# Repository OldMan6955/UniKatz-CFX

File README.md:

# UniKatz-CFX
UWU x CAT x Love x Peace is all we need

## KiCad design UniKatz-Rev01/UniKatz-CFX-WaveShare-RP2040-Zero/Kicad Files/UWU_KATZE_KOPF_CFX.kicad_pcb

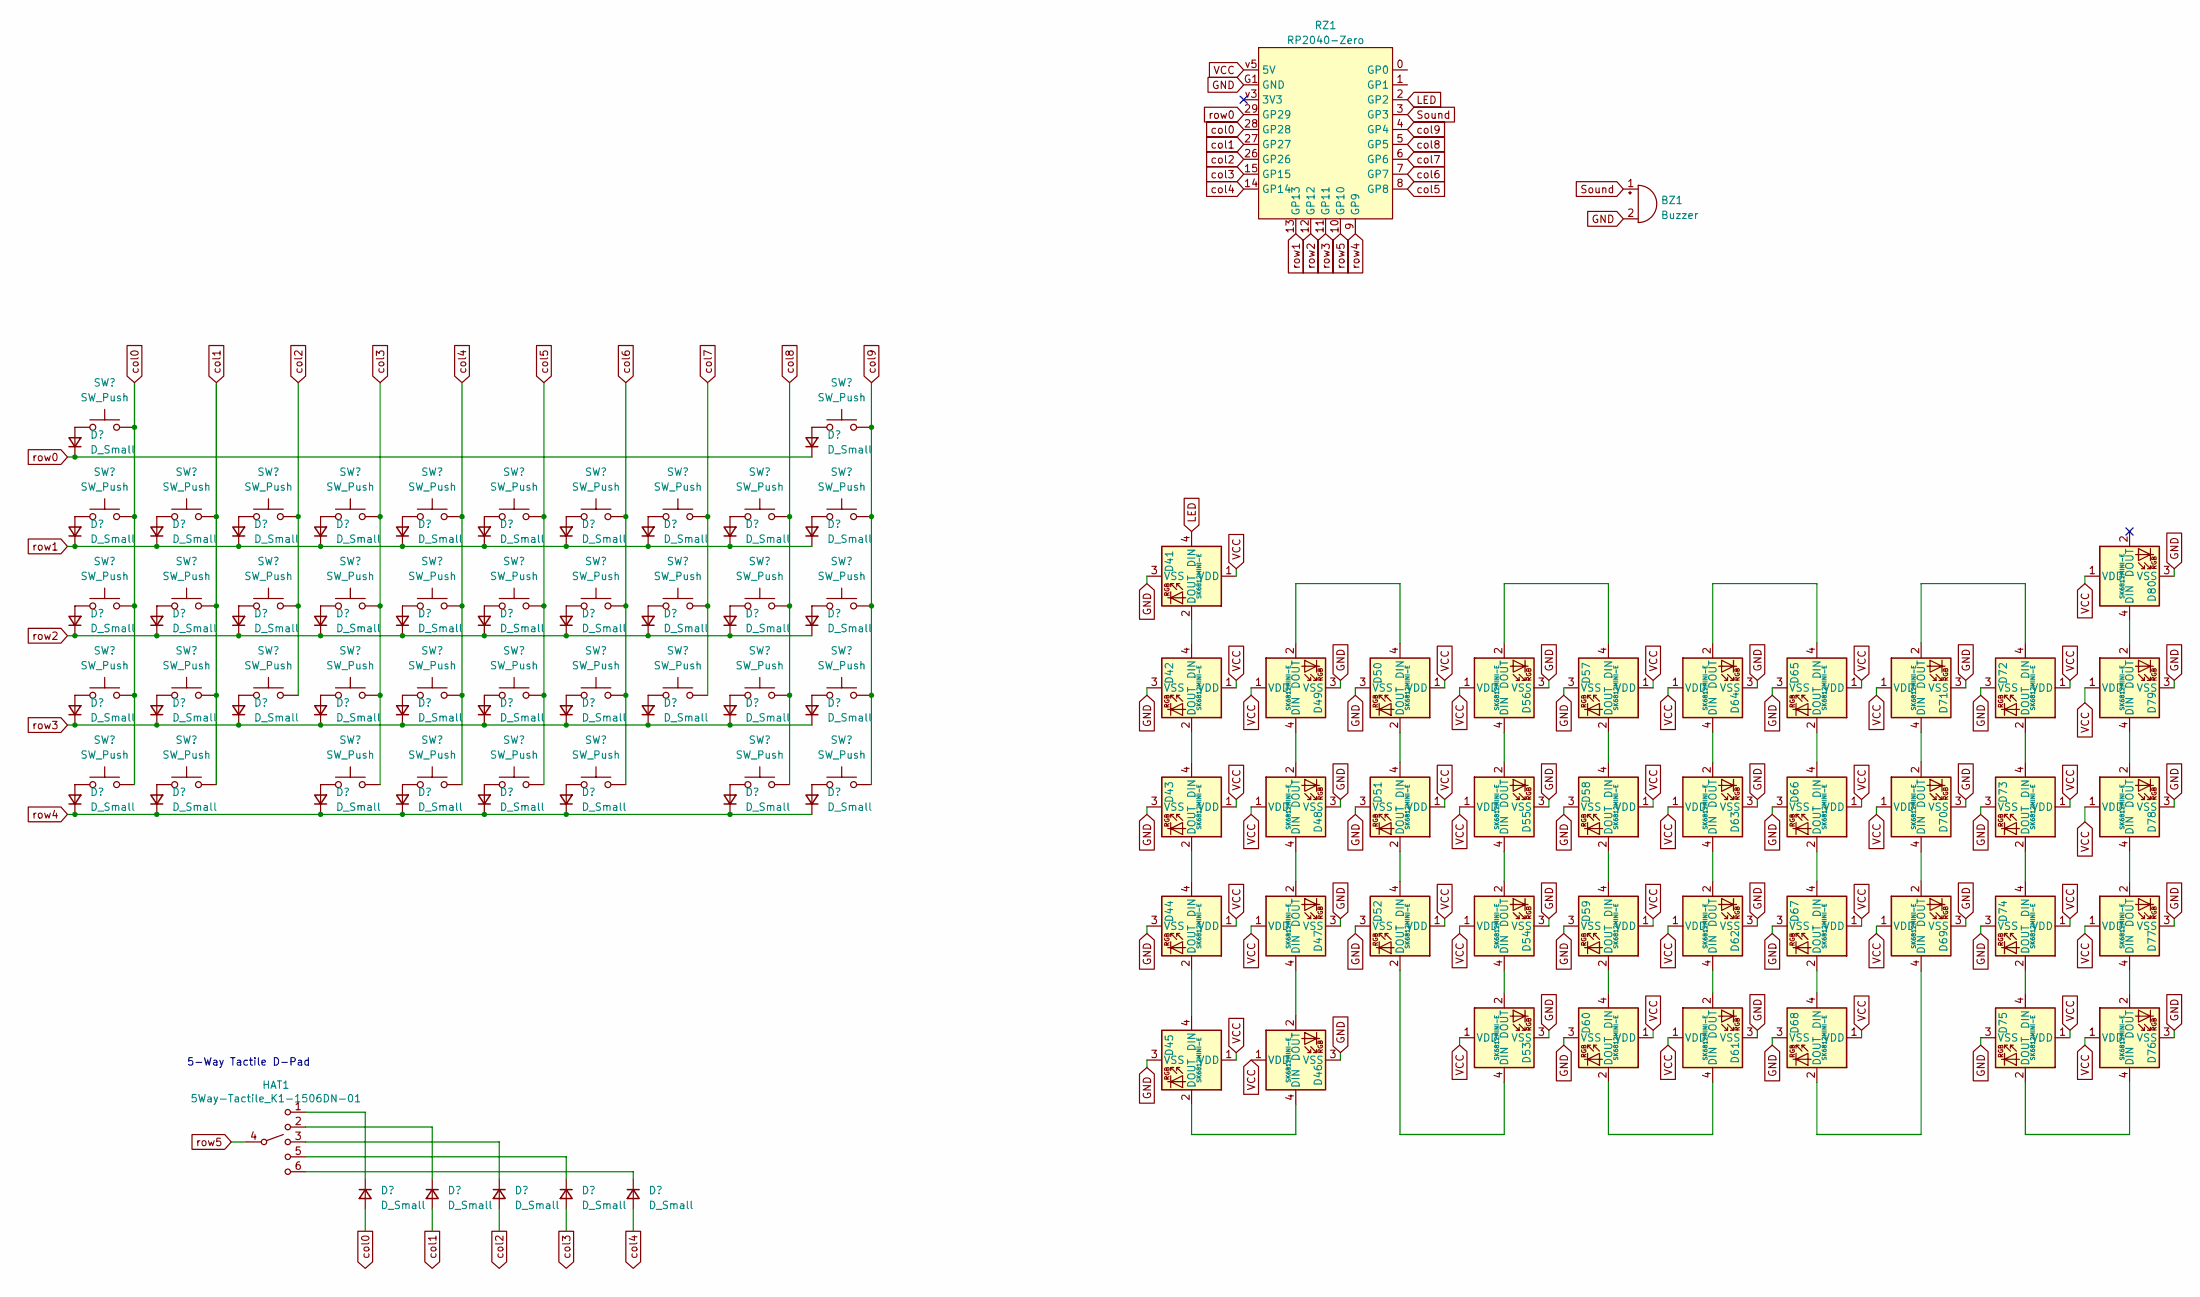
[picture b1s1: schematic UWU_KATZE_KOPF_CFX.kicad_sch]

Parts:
BZ1: Buzzer; Buzzer_Mallory_AST1109MLTRQ
D1, D2, D3, D4, D5, D6, D7, D8, D9, D10, D11, D12, D13, D14, D15, D16, D17, D18, D19, D20, D21, D22, D23, D24, D25, D26, D27, D28, D29, D30, D31, D32, D33, D34, D35, D36, D37, D38, D39, D40, D81, D82, D83, D84, D85: D_Small; Diode_SOD123 triangle clean
D41, D42, D43, D44, D45, D46, D47, D48, D49, D50, D51, D52, D53, D54, D55, D56, D57, D58, D59, D60, D61, D62, D63, D64, D65, D66, D67, D68, D69, D70, D71, D72, D73, D74, D75, D76, D77, D78, D79, D80: SK6812MINI-E; SK6812-MINI-E mit LED v2
HAT1: 5Way-Tactile_K1-1506DN-01; 5Way-non-reverse no silk
RZ1: RP2040-Zero; RP2040-Zero mittig
SW1, SW2, SW3, SW4, SW5, SW6, SW7, SW8, SW9, SW10, SW11, SW12, SW13, SW14, SW15, SW16, SW17, SW18, SW19, SW20, SW21, SW22, SW23, SW24, SW25, SW26, SW27, SW28, SW29, SW30, SW31, SW32, SW33, SW34, SW35, SW36, SW37, SW38, SW39, SW40: SW_Push; Kailh_socket_PG1350 LED Window ME Version V2

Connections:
GND: BZ1.2 (+), D41.3 (VSS), D42.3 (VSS), D43.3 (VSS), D44.3 (VSS), D45.3 (VSS), D46.3 (VSS), D47.3 (VSS), D48.3 (VSS), D49.3 (VSS), D50.3 (VSS), D51.3 (VSS), D52.3 (VSS), D53.3 (VSS), D54.3 (VSS), D55.3 (VSS), D56.3 (VSS), D57.3 (VSS), D58.3 (VSS), D59.3 (VSS), D60.3 (VSS), D61.3 (VSS), D62.3 (VSS), D63.3 (VSS), D64.3 (VSS), D65.3 (VSS), D66.3 (VSS), D67.3 (VSS), D68.3 (VSS), D69.3 (VSS), D70.3 (VSS), D71.3 (VSS), D72.3 (VSS), D73.3 (VSS), D74.3 (VSS), D75.3 (VSS), D76.3 (VSS), D77.3 (VSS), D78.3 (VSS), D79.3 (VSS), D80.3 (VSS), RZ1.G1 (GND)
LED: D41.4 (DIN), RZ1.2 (GP2)
unnamed: D1.2 (A), SW1.1
unnamed: D2.2 (A), SW2.1
unnamed: D3.2 (A), SW3.1
unnamed: D4.2 (A), SW4.1
unnamed: D5.2 (A), SW5.1
unnamed: D6.2 (A), SW6.1
unnamed: D7.2 (A), SW7.1
unnamed: D8.2 (A), SW8.1
unnamed: D9.2 (A), SW9.1
unnamed: D10.2 (A), SW10.1
unnamed: D11.2 (A), SW11.1
unnamed: D12.2 (A), SW12.1
unnamed: D13.2 (A), SW13.1
unnamed: D14.2 (A), SW14.1
unnamed: D15.2 (A), SW15.1
unnamed: D16.2 (A), SW16.1
unnamed: D17.2 (A), SW17.1
unnamed: D18.2 (A), SW18.1
unnamed: D19.2 (A), SW19.1
unnamed: D20.2 (A), SW20.1
unnamed: D21.2 (A), SW21.1
unnamed: D22.2 (A), SW22.1
unnamed: D23.2 (A), SW23.1
unnamed: D24.2 (A), SW24.1
unnamed: D25.2 (A), SW25.1
unnamed: D26.2 (A), SW26.1
unnamed: D27.2 (A), SW27.1
unnamed: D28.2 (A), SW28.1
unnamed: D29.2 (A), SW29.1
unnamed: D30.2 (A), SW30.1
unnamed: D31.2 (A), SW31.1
unnamed: D32.2 (A), SW32.1
unnamed: D33.2 (A), SW33.1
unnamed: D34.2 (A), SW34.1
unnamed: D35.2 (A), SW35.1
unnamed: D36.2 (A), SW36.1
unnamed: D37.2 (A), SW37.1
unnamed: D38.2 (A), SW38.1
unnamed: D39.2 (A), SW39.1
unnamed: D40.2 (A), SW40.1
unnamed: D41.2 (DOUT), D42.4 (DIN)
unnamed: D42.2 (DOUT), D43.4 (DIN)
unnamed: D43.2 (DOUT), D44.4 (DIN)
unnamed: D44.2 (DOUT), D45.4 (DIN)
unnamed: D45.2 (DOUT), D46.4 (DIN)
unnamed: D46.2 (DOUT), D47.4 (DIN)
unnamed: D47.2 (DOUT), D48.4 (DIN)
unnamed: D48.2 (DOUT), D49.4 (DIN)
unnamed: D49.2 (DOUT), D50.4 (DIN)
unnamed: D50.2 (DOUT), D51.4 (DIN)
unnamed: D51.2 (DOUT), D52.4 (DIN)
unnamed: D52.2 (DOUT), D53.4 (DIN)
unnamed: D53.2 (DOUT), D54.4 (DIN)
unnamed: D54.2 (DOUT), D55.4 (DIN)
unnamed: D55.2 (DOUT), D56.4 (DIN)
unnamed: D56.2 (DOUT), D57.4 (DIN)
unnamed: D57.2 (DOUT), D58.4 (DIN)
unnamed: D58.2 (DOUT), D59.4 (DIN)
unnamed: D59.2 (DOUT), D60.4 (DIN)
unnamed: D60.2 (DOUT), D61.4 (DIN)
unnamed: D61.2 (DOUT), D62.4 (DIN)
unnamed: D62.2 (DOUT), D63.4 (DIN)
unnamed: D63.2 (DOUT), D64.4 (DIN)
unnamed: D64.2 (DOUT), D65.4 (DIN)
unnamed: D65.2 (DOUT), D66.4 (DIN)
unnamed: D66.2 (DOUT), D67.4 (DIN)
unnamed: D67.2 (DOUT), D68.4 (DIN)
unnamed: D68.2 (DOUT), D69.4 (DIN)
unnamed: D69.2 (DOUT), D70.4 (DIN)
unnamed: D70.2 (DOUT), D71.4 (DIN)
unnamed: D71.2 (DOUT), D72.4 (DIN)
unnamed: D72.2 (DOUT), D73.4 (DIN)
unnamed: D73.2 (DOUT), D74.4 (DIN)
unnamed: D74.2 (DOUT), D75.4 (DIN)
unnamed: D75.2 (DOUT), D76.4 (DIN)
unnamed: D76.2 (DOUT), D77.4 (DIN)
unnamed: D77.2 (DOUT), D78.4 (DIN)
unnamed: D78.2 (DOUT), D79.4 (DIN)
unnamed: D79.2 (DOUT), D80.4 (DIN)
unnamed: D81.1 (K), HAT1.1
unnamed: D82.1 (K), HAT1.2
unnamed: D83.1 (K), HAT1.3
unnamed: D84.1 (K), HAT1.5
unnamed: D85.1 (K), HAT1.6
Sound: BZ1.1 (-), RZ1.3 (GP3)
VCC: D41.1 (VDD), D42.1 (VDD), D43.1 (VDD), D44.1 (VDD), D45.1 (VDD), D46.1 (VDD), D47.1 (VDD), D48.1 (VDD), D49.1 (VDD), D50.1 (VDD), D51.1 (VDD), D52.1 (VDD), D53.1 (VDD), D54.1 (VDD), D55.1 (VDD), D56.1 (VDD), D57.1 (VDD), D58.1 (VDD), D59.1 (VDD), D60.1 (VDD), D61.1 (VDD), D62.1 (VDD), D63.1 (VDD), D64.1 (VDD), D65.1 (VDD), D66.1 (VDD), D67.1 (VDD), D68.1 (VDD), D69.1 (VDD), D70.1 (VDD), D71.1 (VDD), D72.1 (VDD), D73.1 (VDD), D74.1 (VDD), D75.1 (VDD), D76.1 (VDD), D77.1 (VDD), D78.1 (VDD), D79.1 (VDD), D80.1 (VDD), RZ1.v5 (5V)
col0: D81.2 (A), RZ1.28 (GP28), SW1.2, SW3.2, SW13.2, SW23.2, SW33.2
col1: D82.2 (A), RZ1.27 (GP27), SW4.2, SW14.2, SW24.2, SW34.2
col2: D83.2 (A), RZ1.26 (GP26), SW5.2, SW15.2, SW25.2
col3: D84.2 (A), RZ1.15 (GP15), SW6.2, SW16.2, SW26.2, SW35.2
col4: D85.2 (A), RZ1.14 (GP14), SW7.2, SW17.2, SW27.2, SW36.2
col5: RZ1.8 (GP8), SW8.2, SW18.2, SW28.2, SW37.2
col6: RZ1.7 (GP7), SW9.2, SW19.2, SW29.2, SW38.2
col7: RZ1.6 (GP6), SW10.2, SW20.2, SW30.2
col8: RZ1.5 (GP5), SW11.2, SW21.2, SW31.2, SW39.2
col9: RZ1.4 (GP4), SW2.2, SW12.2, SW22.2, SW32.2, SW40.2
row0: D1.1 (K), D2.1 (K), RZ1.29 (GP29)
row1: D3.1 (K), D4.1 (K), D5.1 (K), D6.1 (K), D7.1 (K), D8.1 (K), D9.1 (K), D10.1 (K), D11.1 (K), D12.1 (K), RZ1.13 (GP13)
row2: D13.1 (K), D14.1 (K), D15.1 (K), D16.1 (K), D17.1 (K), D18.1 (K), D19.1 (K), D20.1 (K), D21.1 (K), D22.1 (K), RZ1.12 (GP12)
row3: D23.1 (K), D24.1 (K), D25.1 (K), D26.1 (K), D27.1 (K), D28.1 (K), D29.1 (K), D30.1 (K), D31.1 (K), D32.1 (K), RZ1.11 (GP11)
row4: D33.1 (K), D34.1 (K), D35.1 (K), D36.1 (K), D37.1 (K), D38.1 (K), D39.1 (K), D40.1 (K), RZ1.9 (GP9)
row5: HAT1.4, RZ1.10 (GP10)

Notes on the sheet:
5-Way Tactile D-Pad

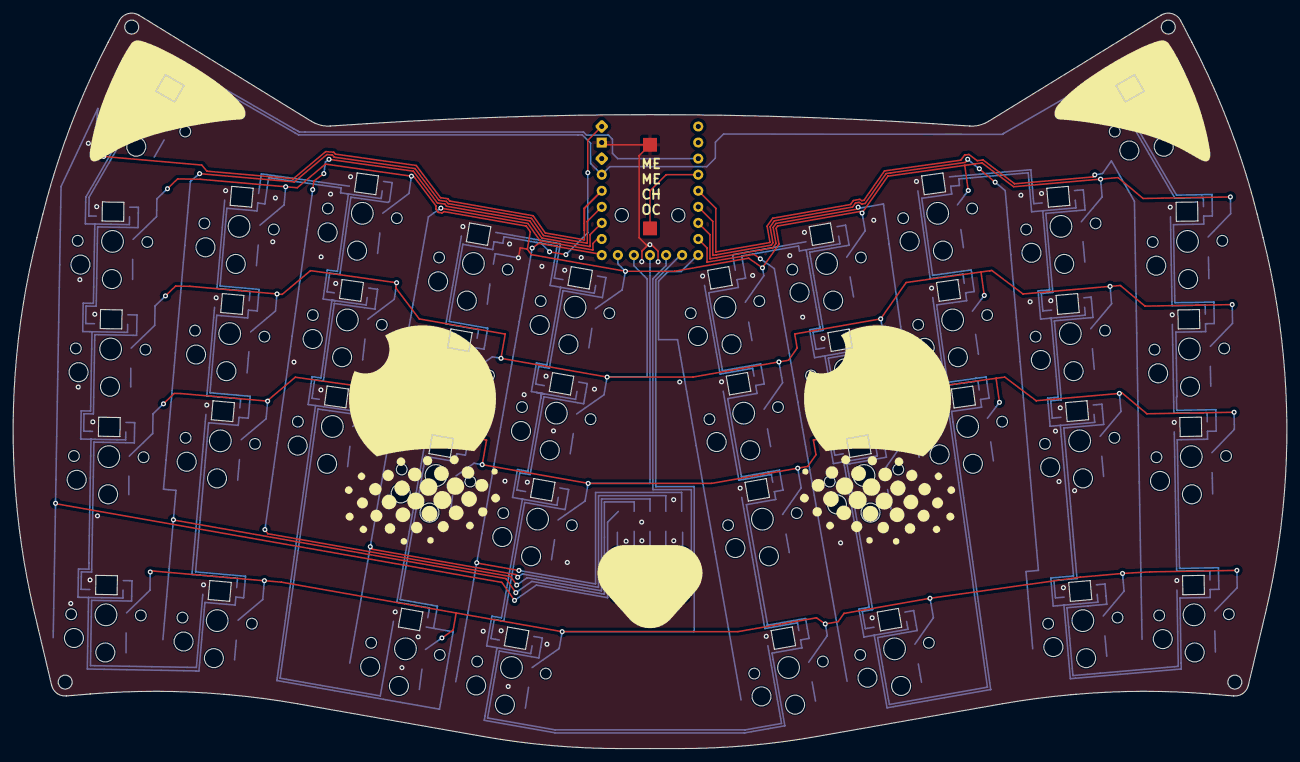
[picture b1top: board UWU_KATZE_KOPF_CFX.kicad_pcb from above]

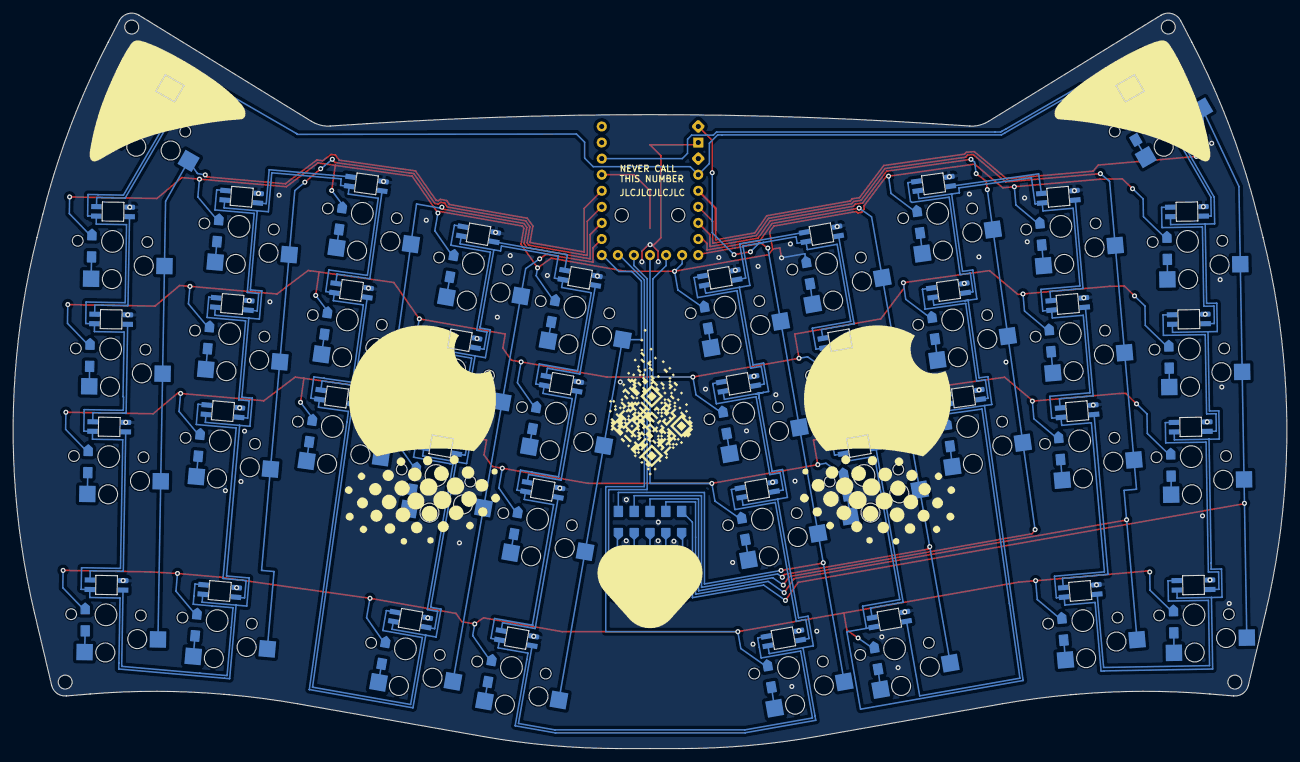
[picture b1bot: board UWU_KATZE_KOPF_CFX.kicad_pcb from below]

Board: 2 copper layers, 201.2 x 116.2 mm, 128 parts (85 on the bottom side), 104 nets.

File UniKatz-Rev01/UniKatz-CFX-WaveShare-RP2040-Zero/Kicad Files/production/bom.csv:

Designator,Footprint,Quantity,Value,LCSC Part #
BZ1,Buzzer_Mallory_AST1109MLTRQ,1,Buzzer,
"D1, D10, D11, D12, D13, D14, D15, D16, D17, D18, D19, D2, D20, D21, D22, D23, D24, D25, D26, D27, D28, D29, D3, D30, D31, D32, D33, D34, D35, D36, D37, D38, D39, D4, D40, D5, D6, D7, D8, D81, D82, D83, D84, D85, D9",Diode_SOD123 triangle clean,45,D_Small,
"D41, D42, D43, D44, D45, D46, D47, D48, D49, D50, D51, D52, D53, D54, D55, D56, D57, D58, D59, D60, D61, D62, D63, D64, D65, D66, D67, D68, D69, D70, D71, D72, D73, D74, D75, D76, D77, D78, D79, D80",SK6812-MINI-E mit LED v2 ohne silk LED FRAME,40,SK6812MINI-E,
HAT1,5Way-non-reverse no silk,1,5Way-Tactile_K1-1506DN-01,
RZ1,RP2040-Zero mittig,1,RP2040-Zero,
"SW1, SW10, SW11, SW12, SW13, SW14, SW15, SW16, SW17, SW18, SW19, SW2, SW20, SW21, SW22, SW23, SW24, SW25, SW26, SW27, SW28, SW29, SW3, SW30, SW31, SW32, SW33, SW34, SW35, SW36, SW37, SW38, SW39, SW4, SW40, SW5, SW6, SW7, SW8, SW9",Kailh_socket_PG1350 LED Window ME Version V2,40,SW_Push,
